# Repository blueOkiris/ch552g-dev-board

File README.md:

# CH552G Dev Board

## Description

A simple breakout board with minimal hardware design for the CH552g as well as a C project to be used as a basis.

I've become fond of the CH552g for projects as it's simple like AVR unlike something like ARM, but it doesn't require a programmer and has built-in USB support from the factory, unlike something like AVR but like ARM.

To ensure I don't have to constantly order pcb after pcb, I've created this dev board that can go on a breadboard, so I can prototype with the chip more easily.

## Order Boards

Open up KiCAD and export the Gerber and Drill files and zip them up or grab a zip from Releases.

Then go to JLCPCB's website, start a new order with the zip file, and select PCB Assembly.

Then upload the provided BOM and CPL (in the pcb/ folder) and submit an order.

## Build Example Code 

First, clone the repo, then make sure you clone all submodules: `git submodule update --init --recursive`

### Dependencies

- Linux:
   + Just use [nix](https://nixos.org/download/). Use `nix-shell` to get the following:
      - gnumake
      - hidapi
      - libusb1
      - libusb
      - python3
      - sdcc
      - virtualenv which will create .venv w/
         + pyusb
         + ch55xtool
- Windows:
   + Install [sdcc](https://sourceforge.net/projects/sdcc/files/latest/download?source=files)
   + Install [mingw](https://sourceforge.net/projects/mingw/files/latest/download)
   + Install [WCHISPTool](https://www.wch.cn/download/WCHISPTool_Setup_exe.html)
      - Only relevant for uploading, not building

### Build

On Linux, make sure you have the python virtualenv active and sdcc in your path (this happens every time you run `nix-shell`)

Run `make -C example-code` (or `mingw32-make -C example-code`), and it will build everything.

### Upload

__Linux:__

Assuming the program has been built, to upload:

1. Hold down a button on the board you want to upload to
2. Plug into USB and let go of the button
3. Within 2 seconds of letting go, run `make -C example-code upload`

If it fails, just try again a few times. If it's still not working, then repeat the process.

__Windows:__

Use WCHISP Studio

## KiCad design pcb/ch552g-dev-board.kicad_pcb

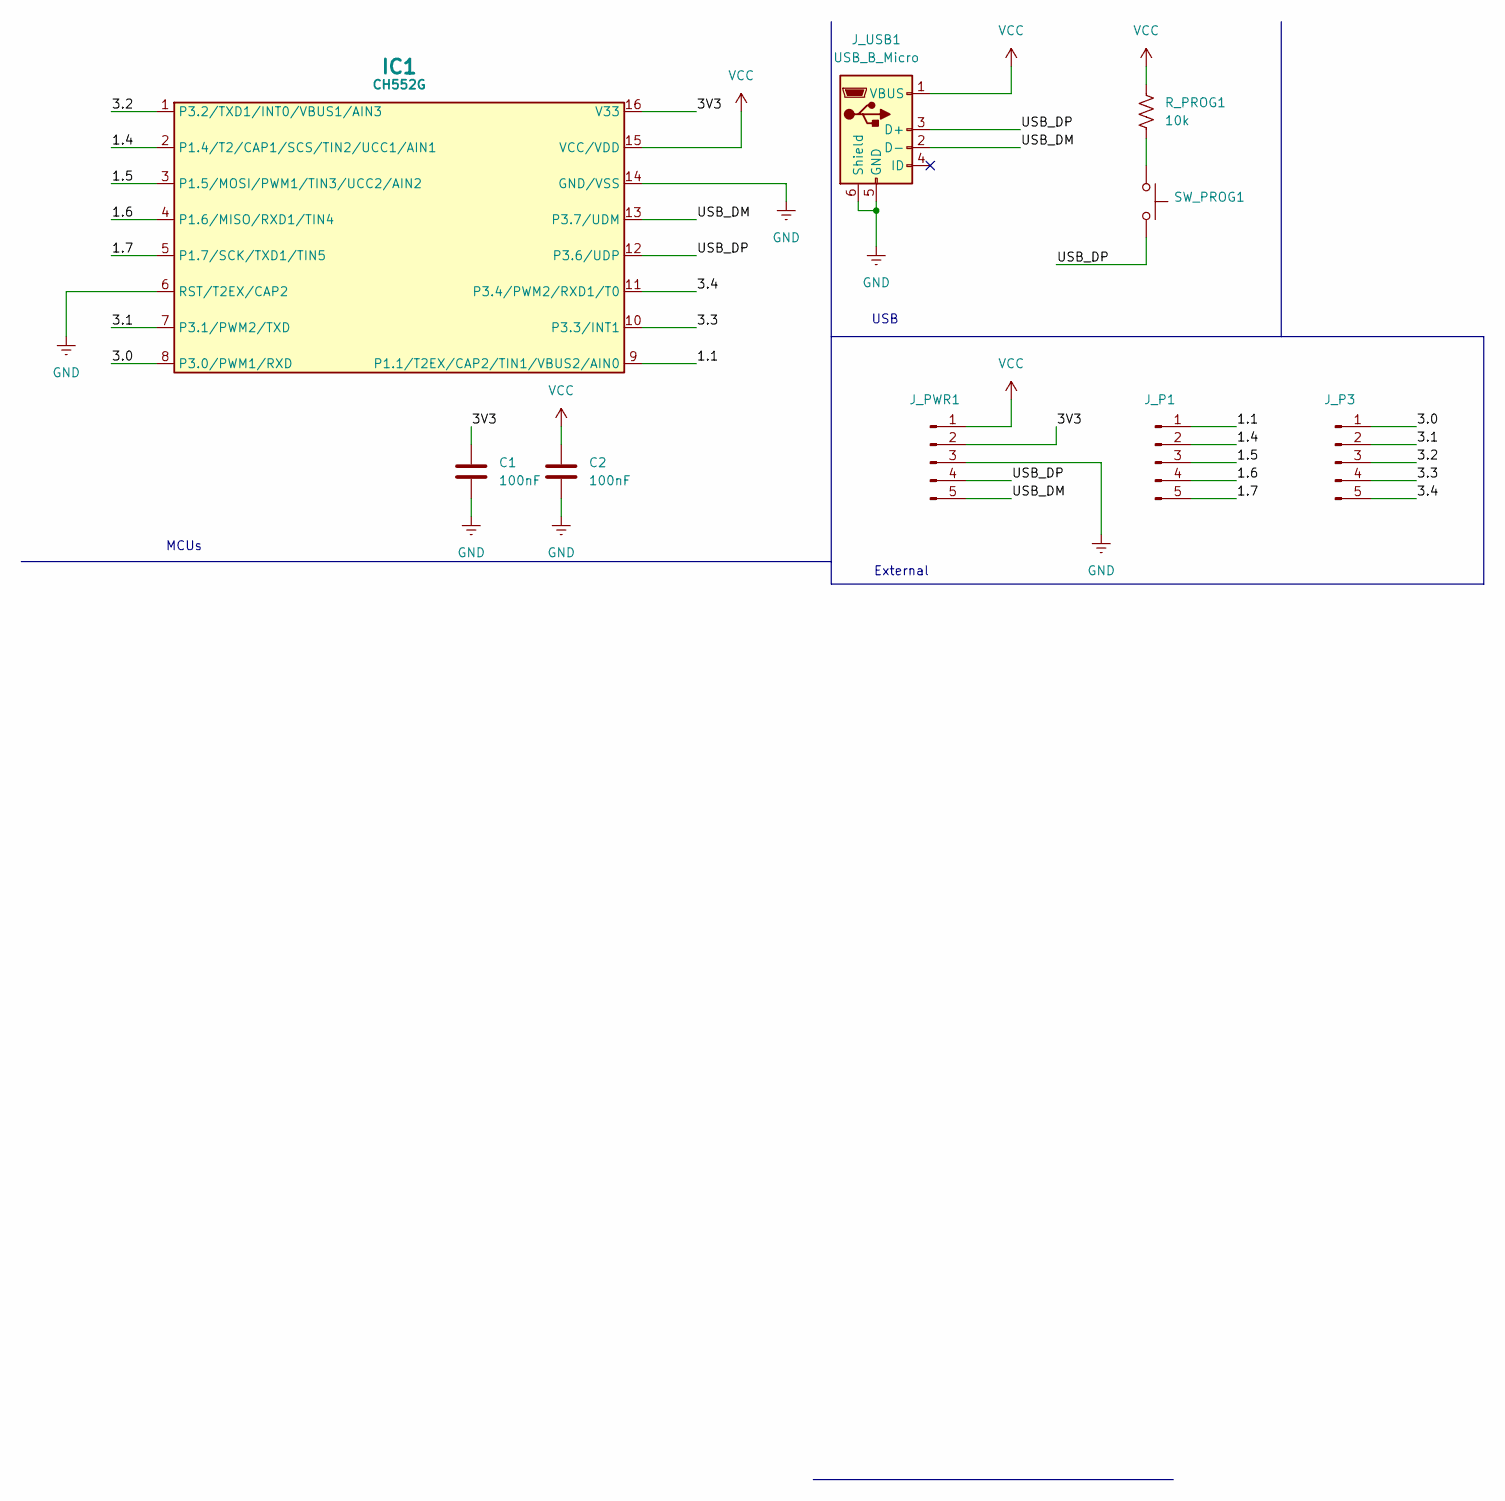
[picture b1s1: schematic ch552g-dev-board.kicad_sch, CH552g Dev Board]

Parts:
C1, C2: 100nF; C_0603_1608Metric
IC1: CH552G; SOIC-16_3.9x9.9mm_Pitch1.27mm
J_P1, J_P3: PinHeader_1x05_P2.54mm_Vertical
J_PWR1: PinHeader_1x05_P2.54mm_Vertical
J_USB1: USB_B_Micro; USB_Micro-B_Amphenol_10118194_Horizontal
R_PROG1: 10k; R_0603_1608Metric
SW_PROG1: SW_Push_1P1T_NO_6x6mm_H9.5mm

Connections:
/1.1: IC1.9 (P1.1/T2EX/CAP2/TIN1/VBUS2/AIN0), J_P1.1
/1.4: IC1.2 (P1.4/T2/CAP1/SCS/TIN2/UCC1/AIN1), J_P1.2
/1.5: IC1.3 (P1.5/MOSI/PWM1/TIN3/UCC2/AIN2), J_P1.3
/1.6: IC1.4 (P1.6/MISO/RXD1/TIN4), J_P1.4
/1.7: IC1.5 (P1.7/SCK/TXD1/TIN5), J_P1.5
/3.0: IC1.8 (P3.0/PWM1/RXD), J_P3.1
/3.1: IC1.7 (P3.1/PWM2/TXD), J_P3.2
/3.2: IC1.1 (P3.2/TXD1/INT0/VBUS1/AIN3), J_P3.3
/3.3: IC1.10 (P3.3/INT1), J_P3.4
/3.4: IC1.11 (P3.4/PWM2/RXD1/T0), J_P3.5
/3V3: C1.1, IC1.16 (V33), J_PWR1.2
/USB_DM: IC1.13 (P3.7/UDM), J_PWR1.5, J_USB1.2 (D-)
/USB_DP: IC1.12 (P3.6/UDP), J_PWR1.4, J_USB1.3 (D+), SW_PROG1.2
GND: C1.2, C2.2, IC1.6 (RST/T2EX/CAP2), IC1.14 (GND/VSS), J_PWR1.3, J_USB1.5 (GND), J_USB1.6 (Shield)
unnamed: R_PROG1.2, SW_PROG1.1
VCC: C2.1, IC1.15 (VCC/VDD), J_PWR1.1, J_USB1.1 (VBUS), R_PROG1.1

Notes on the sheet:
External
USB
MCUs

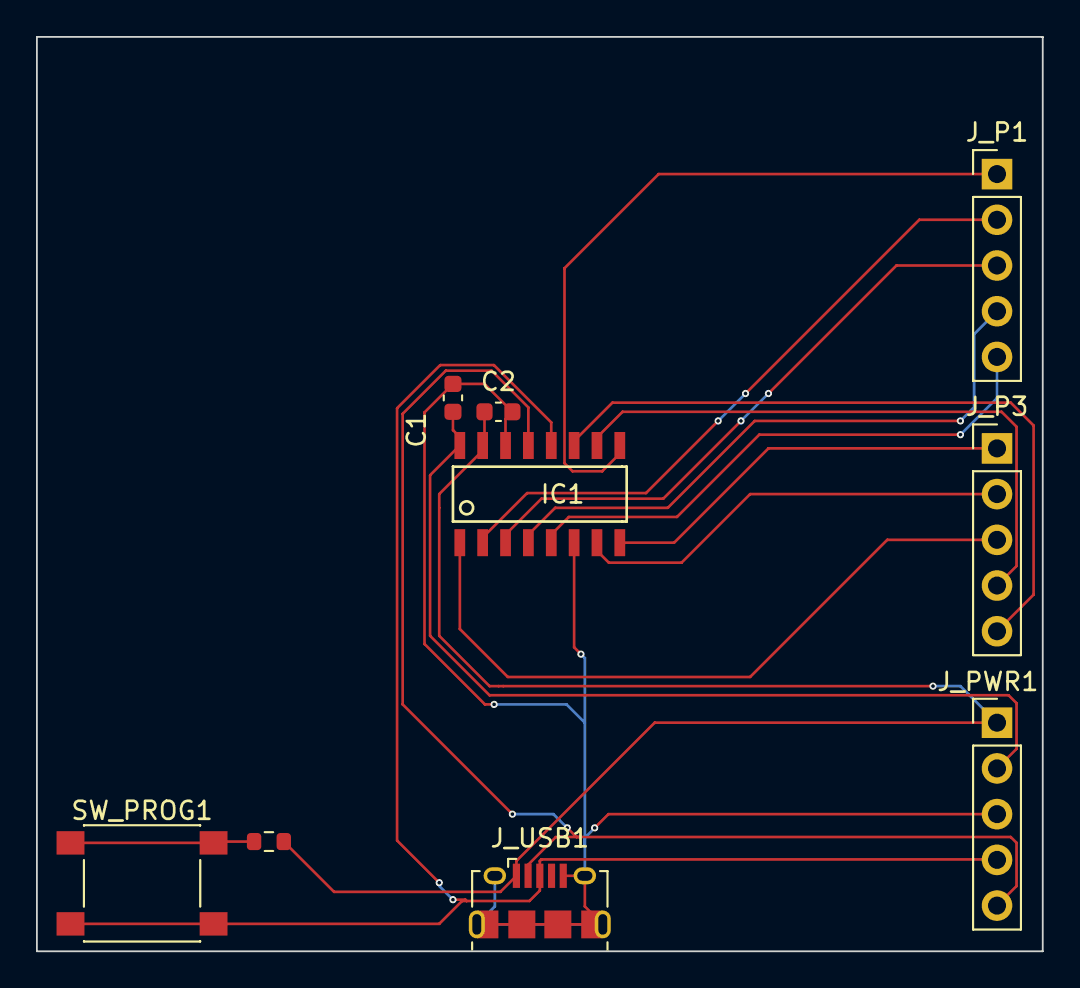
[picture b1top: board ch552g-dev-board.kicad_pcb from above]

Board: 2 copper layers, 55.9 x 50.8 mm, 9 parts (0 on the bottom side), 16 nets.

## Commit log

2024-04-19 Rev 1
2024-04-19 README: add motivations, ordering, and status note
2024-04-19 README: note the software
2024-04-25 Removed lock board
2024-04-26 README: rm r1 note
2024-04-26 README: add dev board
2024-04-26 ch552g-dev-board.jpg: added
2024-04-26 README: /game/program/
2024-04-26 README: noted downloading file from release
